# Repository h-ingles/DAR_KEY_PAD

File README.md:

# DAR_KEY_PAD
The Dumb As Rocks Key Pad for the 8BitDo retro keyboard. A single 8 button keypad equivalent to 4 8BitDo Dual Super Buttons. Probably usable elsewhere, but also just as probable that it's a bad idea.

# SUMMARY
The Dumb As Rocks (DAR) Key Pad is a single-sided integrated replacement of 4 8BitDo Dual Super Buttons. There are absolutely no brains on board. Only 12 passive components, 4 audio cables, and a handful of screws and standoffs are required to use this pad. The absolute minimum of design work has been done on this board. At present, it is designed to be easily manufactured, easily readable, and easily modifyable. With some modification, it is likely possible to CNC mill this keypad on copper clad board.

Should this have been a PCB? No. Boredom is a hell of a thing.

# DETAILS

## THE JACKS
The 8BitDo Retro line of keyboards possess a unique feature. Specifically, the keyboard supports the use of 10 programmable buttons, but 8 of them are modular. The modular buttons are coupled up, and bound to individual 3.5mm "audio" jacks on the back of the keyboard. What makes this novel is that different devices can be attached to these ports juch as joysticks. The rest is handled in OEM software.

Annoyingly, each jack isn't indexed by number, but by letters frequently found on a standard controller. A, B, X, and Y. This gets even more confusing when the peripherals are attached.

## THE BUTTONS
The pinout of the 3.5mm jack/plug is:

Sleeve: VCC

Ring: A button

Tip: B button

The Super Buttons are the perfect example of a minimum viable product stuffed into a nice case (affectionately). The only components in a Super Button are cable, a switch, a carrier PCB (sometimes), and maybe a socket. All electronics to handle the button, such as pull down resistors, debouncing, and diodes are integrated into the keyboard itself. This makes the peripherals inexpensive. More importantly, this makes them easy to build yourself.

Most peripherals, like the jacks, are labeled in the order A, and B. On some occasions X, and Y are used. What makes this frustrating is that while it's labeled the same way the jacks are indexed, how the buttons are indexed is by number. This means "B on X" would be 8, or "A on A" would be 3.

On the DAR KEY PAD, the format [JACK].[INPUT] is used when labeleing the buttons to minimise confusion. Confusion will still likely occur (I'm not stupid, you're stupid!).

## THE PARTS
Aside from the PCB, only the following parts are required to assemble and use the DAR KEY PAD on an 8BitDo Retro keyboard:

4x SJ1-3523N or compatible (ex. uxcell a12062600ux0366)

8x Cherry MX Compatible Keyswitch

8x Cherry-style 1x1 keycaps

4x 3.5mm aux cables, 1.5 ft. or longer

4x M2 machine screws

4x M2 standoffs

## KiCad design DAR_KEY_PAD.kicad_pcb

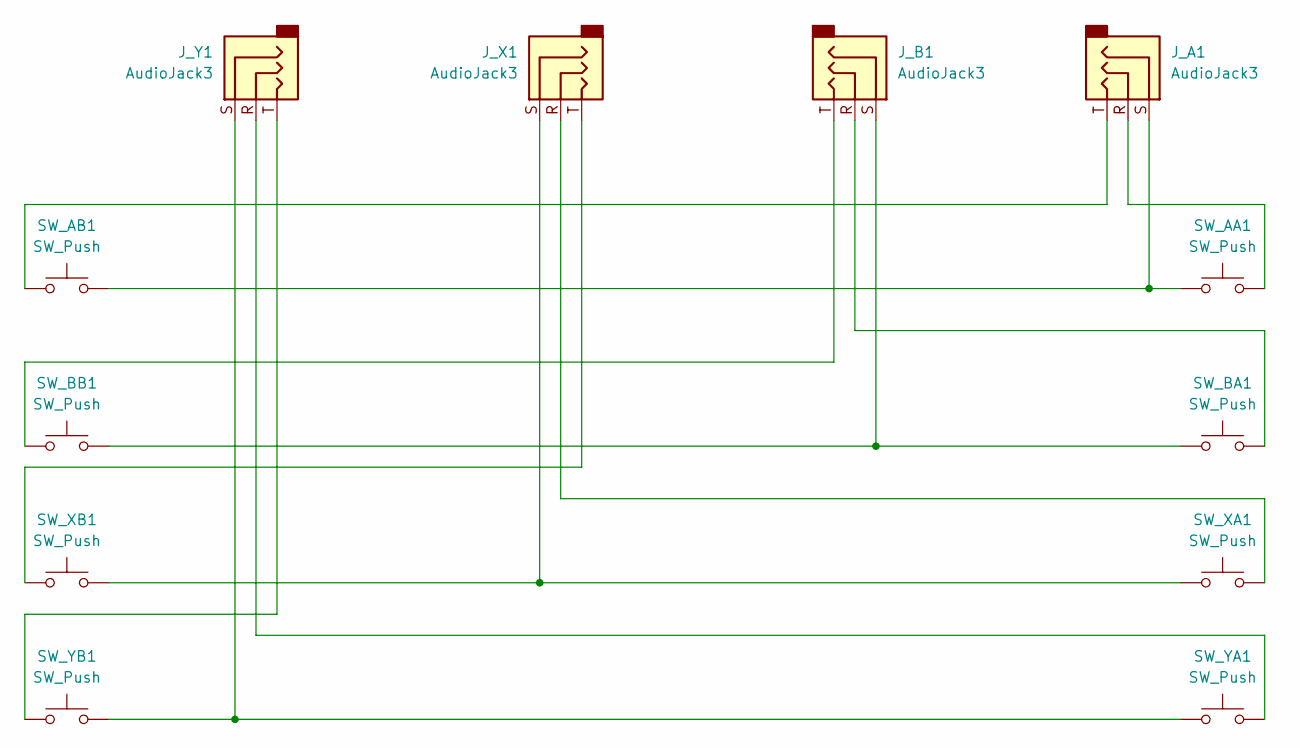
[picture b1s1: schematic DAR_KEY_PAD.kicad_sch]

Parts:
J_A1: AudioJack3; Jack_3.5mm_CUI_SJ1-3523N_Horizontal
J_B1: AudioJack3; Jack_3.5mm_CUI_SJ1-3523N_Horizontal
J_X1: AudioJack3; Jack_3.5mm_CUI_SJ1-3523N_Horizontal
J_Y1: AudioJack3; Jack_3.5mm_CUI_SJ1-3523N_Horizontal
SW_AA1: SW_Push; SW_Cherry_MX_1.00u_PCB
SW_AB1: SW_Push; SW_Cherry_MX_1.00u_PCB
SW_BA1: SW_Push; SW_Cherry_MX_1.00u_PCB
SW_BB1: SW_Push; SW_Cherry_MX_1.00u_PCB
SW_XA1: SW_Push; SW_Cherry_MX_1.00u_PCB
SW_XB1: SW_Push; SW_Cherry_MX_1.00u_PCB
SW_YA1: SW_Push; SW_Cherry_MX_1.00u_PCB
SW_YB1: SW_Push; SW_Cherry_MX_1.00u_PCB

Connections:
unnamed: J_A1.R, SW_AA1.1
unnamed: J_A1.S, SW_AA1.2, SW_AB1.2
unnamed: J_A1.T, SW_AB1.1
unnamed: J_B1.R, SW_BA1.1
unnamed: J_B1.S, SW_BA1.2, SW_BB1.2
unnamed: J_B1.T, SW_BB1.1
unnamed: J_X1.R, SW_XA1.1
unnamed: J_X1.S, SW_XA1.2, SW_XB1.2
unnamed: J_X1.T, SW_XB1.1
unnamed: J_Y1.R, SW_YA1.1
unnamed: J_Y1.S, SW_YA1.2, SW_YB1.2
unnamed: J_Y1.T, SW_YB1.1

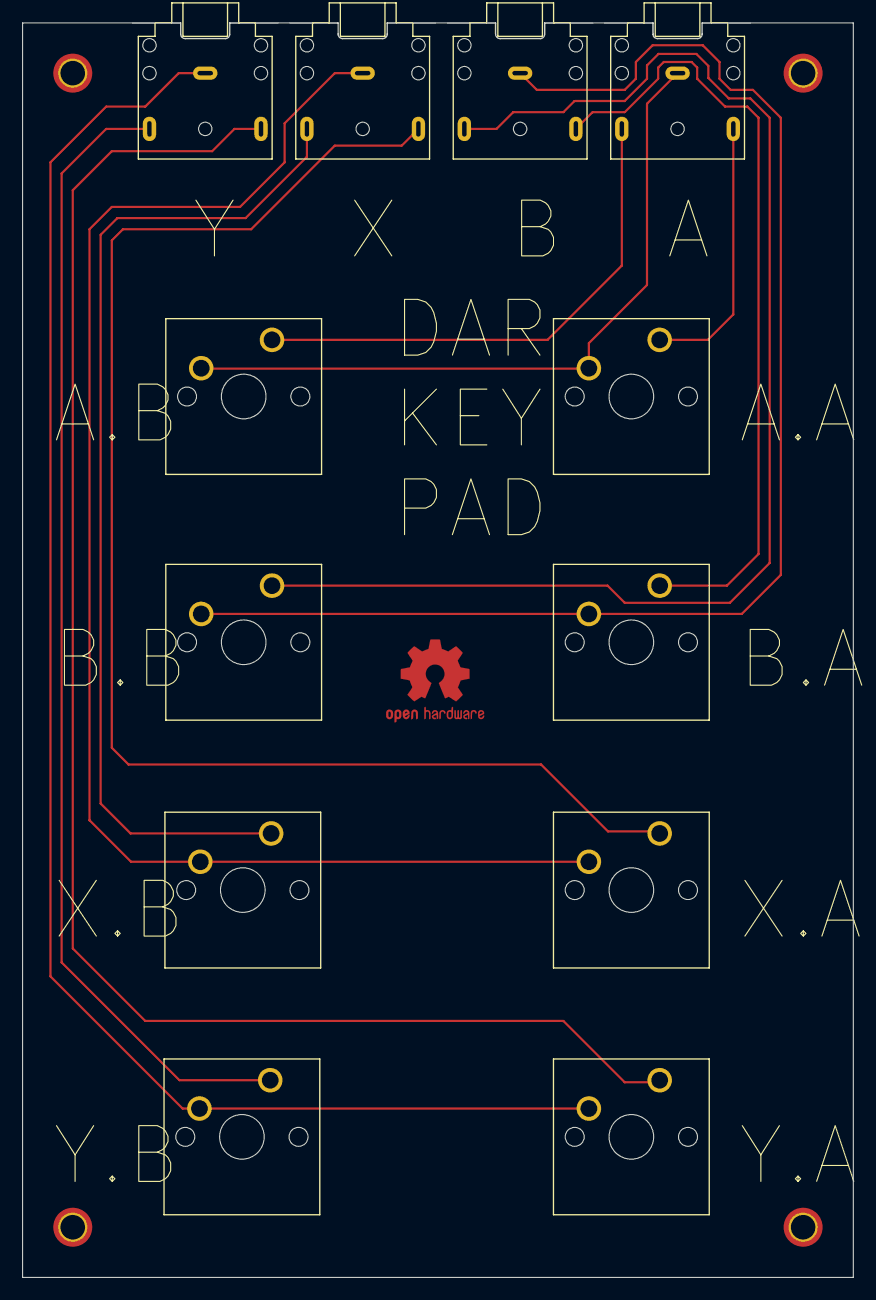
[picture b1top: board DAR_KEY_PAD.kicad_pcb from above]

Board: 2 copper layers, 74.5 x 112.5 mm, 12 parts (0 on the bottom side), 12 nets.

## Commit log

2026-03-29 Initial push.
    Should contain all required files. Contains schematic ("schematic"), PCB, and project file.
2026-04-04 Update README.md
    Made a correction to how Super Buttons are indexed. I've no idea when it changed... Maybe it never did and I'm just insane.
2026-04-18 Create LICENSE
    This really isn't complicated enough to warrant a license, but here's one anyway.
